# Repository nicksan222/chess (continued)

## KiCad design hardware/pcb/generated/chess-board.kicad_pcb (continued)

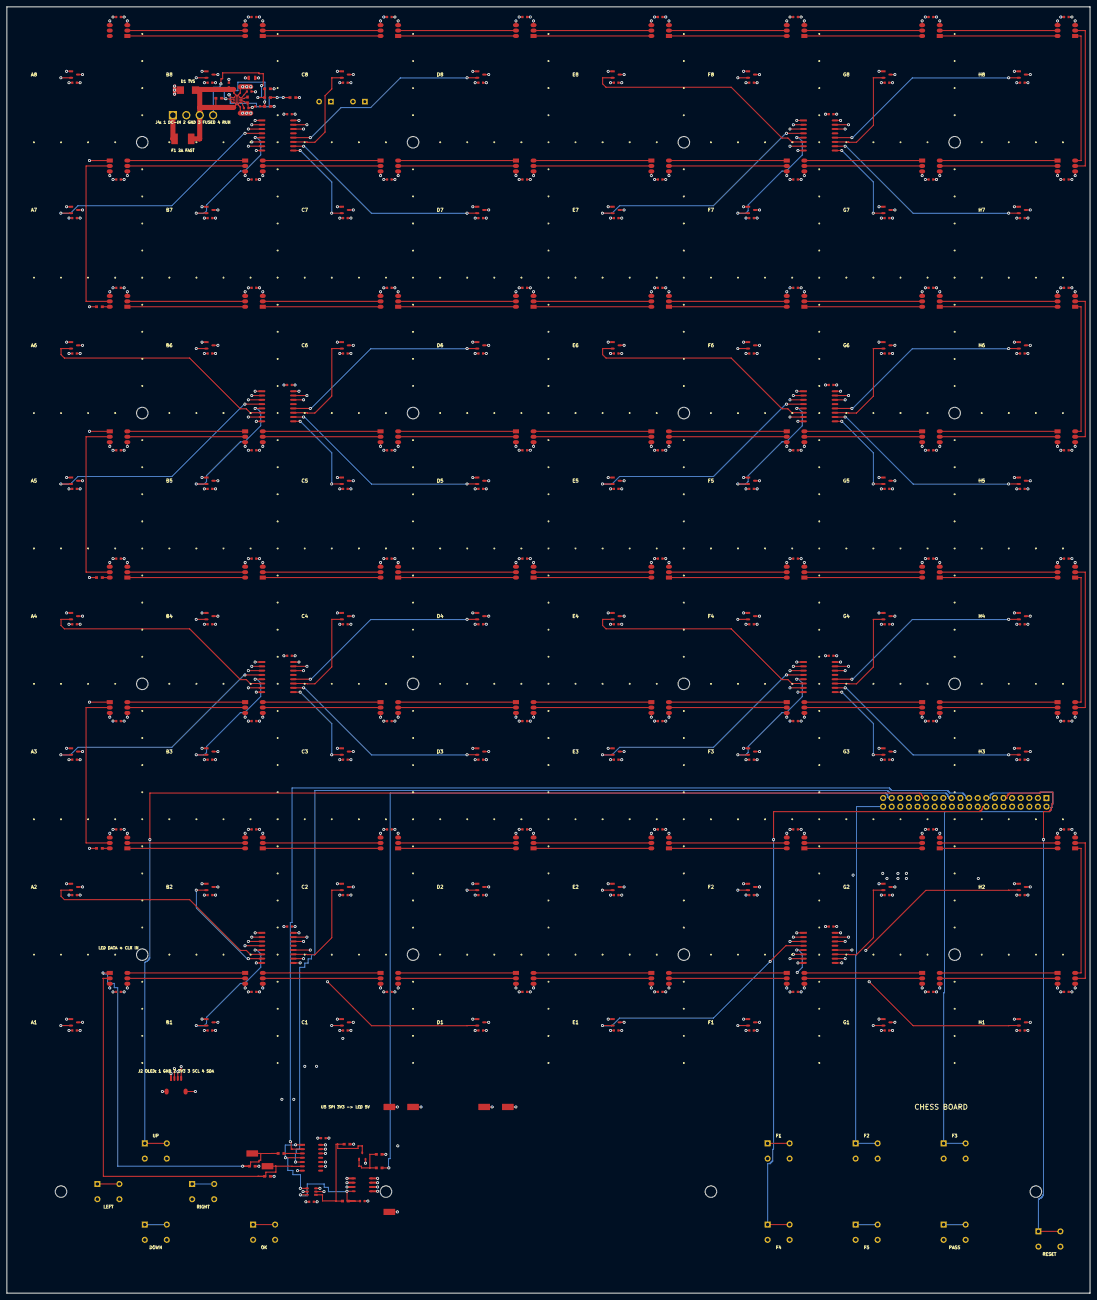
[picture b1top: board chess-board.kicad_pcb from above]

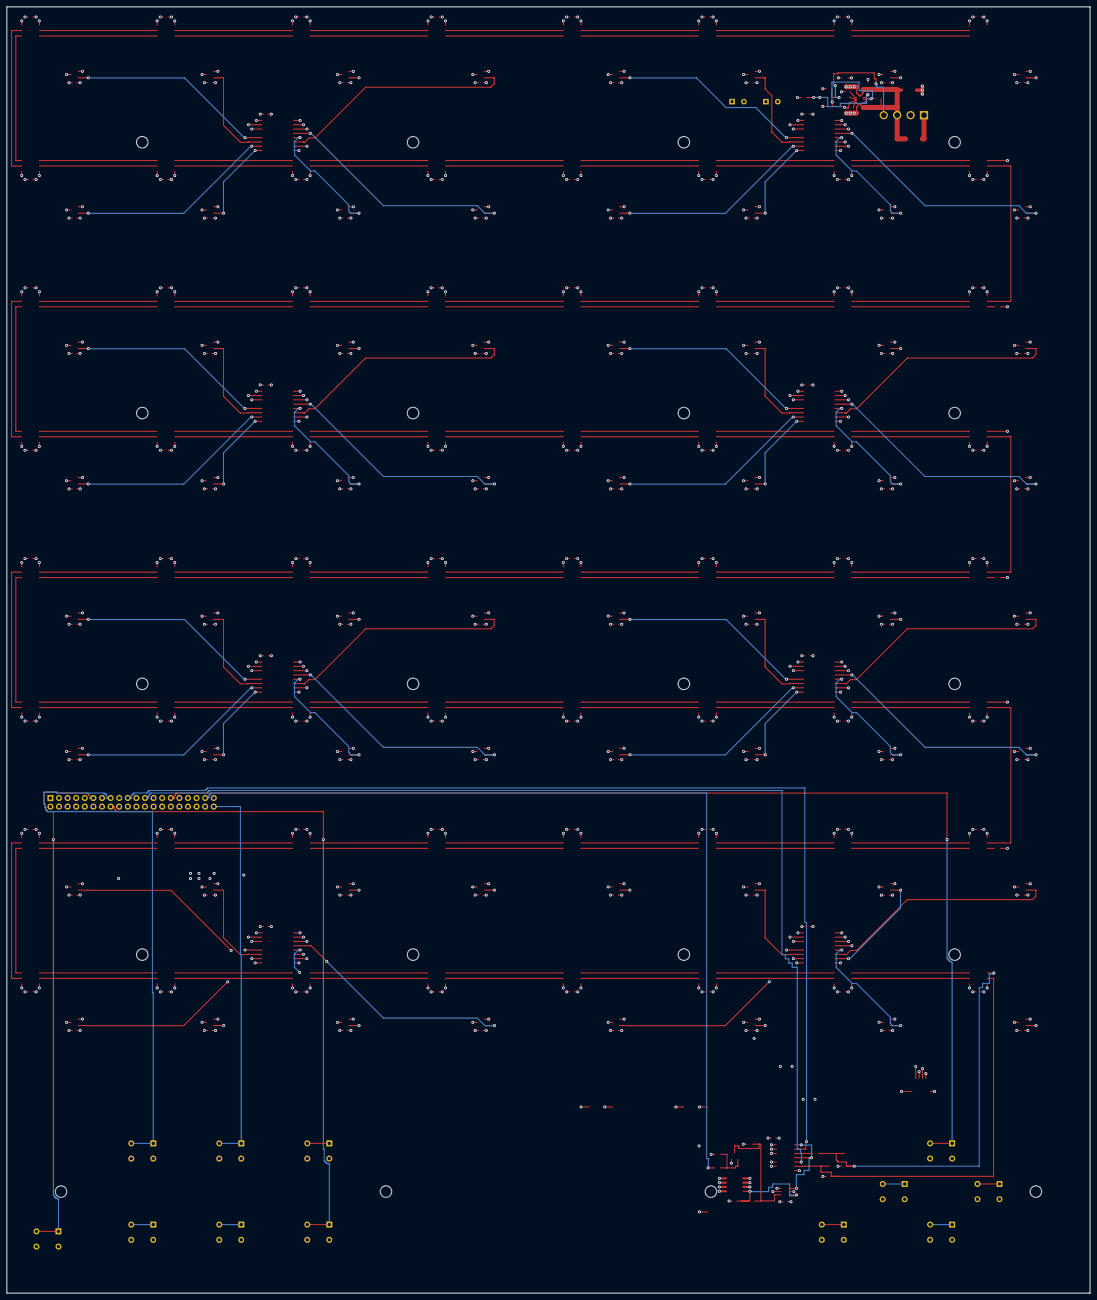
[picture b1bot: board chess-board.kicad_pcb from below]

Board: 8 copper layers, 320.0 x 380.0 mm, 347 parts (4 on the bottom side), 229 nets.

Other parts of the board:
H1, H2, H3, H4, H5, H6, H7, H8, H9, H10, H11, H12, H13, H14, H15, H16, H17, H18, H19, H20: Mounting hole

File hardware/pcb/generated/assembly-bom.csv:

Quantity,Designators,Manufacturer,Manufacturer Part Number,Package,Type
12,"SW1, SW10, SW11, SW12, SW2, SW3, SW4, SW5, SW6, SW7, SW8, SW9",E-Switch,TL1105CF100Q,6x6 mm THT,Through-hole
7,"TP1, TP2, TP3, TP4, TP5, TP6, TP7",Harwin,S1751-46R,SMD test point,SMD
1,J4,JST,B4PS-VH,VH 4P side entry THT,Through-hole
1,J2,JST,SM04B-SRSS-TB,SH 4P side entry SMD,SMD
1,F1,Littelfuse,0453002.MR,2410 fuse,SMD
1,D1,Littelfuse,SMBJ12CA,SMB (DO-214AA),SMD
64,"U10, U11, U12, U13, U14, U15, U16, U17, U18, U19, U20, U21, U22, U23, U24, U25, U26, U27, U28, U29, U30, U31, U32, U33, U34, U35, U36, U37, U38, U39, U40, U41, U42, U43, U44, U45, U46, U47, U48, U49, U50, U51, U52, U53, U54, U55, U56, U57, U58, U59, U6, U60, U61, U62, U63, U64, U65, U66, U67, U68, U69, U7, U8, U9",Opsco Optoelectronics,SK9822-A,PLCC-6 5050,SMD
2,"C1, C140",Rubycon,10ZLJ560M8X11.5,radial 8 mm,Through-hole
1,J1,Sullins Connector Solutions,PPPC202LFBN-RC,2x20 2.54 mm THT,Through-hole
64,"HS1, HS10, HS11, HS12, HS13, HS14, HS15, HS16, HS17, HS18, HS19, HS2, HS20, HS21, HS22, HS23, HS24, HS25, HS26, HS27, HS28, HS29, HS3, HS30, HS31, HS32, HS33, HS34, HS35, HS36, HS37, HS38, HS39, HS4, HS40, HS41, HS42, HS43, HS44, HS45, HS46, HS47, HS48, HS49, HS5, HS50, HS51, HS52, HS53, HS54, HS55, HS56, HS57, HS58, HS59, HS6, HS60, HS61, HS62, HS63, HS64, HS7, HS8, HS9",Texas Instruments,DRV5032FCDBZR,SOT-23-3,SMD
1,U5,Texas Instruments,SN74AHCT125DR,SOIC-14 1.27 mm,SMD
1,U75,Texas Instruments,SN74LVC1G97DBVR,SOT-23-6 (DBV),SMD
8,"U1, U2, U3, U4, U70, U71, U72, U73",Texas Instruments,TCA9554DWR,SOIC-16W 1.27 mm,SMD
1,U74,Texas Instruments,TPS259474ARPWR,VQFN-HR-10 RPW 2x2 mm,SMD
1,Q1,Vishay Siliconix,Si4403DDY-T1-GE3,SO-8 1.27 mm,SMD
1,C141,Yageo,CC0603KRX7R8BB105,0603 (1608 metric),SMD
1,C143,Yageo,CC0603KRX7R9BB102,0603 (1608 metric),SMD
3,"C142, C144, C145",Yageo,CC0603KRX7R9BB103,0603 (1608 metric),SMD
138,"C10, C100, C101, C102, C103, C104, C105, C106, C107, C108, C109, C11, C110, C111, C112, C113, C114, C115, C116, C117, C118, C119, C12, C120, C121, C122, C123, C124, C125, C126, C127, C128, C129, C13, C130, C131, C132, C133, C134, C135, C136, C137, C138, C139, C14, C146, C15, C16, C17, C18, C19, C20, C21, C22, C23, C24, C25, C26, C27, C28, C29, C3, C30, C31, C32, C33, C34, C35, C36, C37, C38, C39, C4, C40, C41, C42, C43, C44, C45, C46, C47, C48, C49, C5, C50, C51, C52, C53, C54, C55, C56, C57, C58, C59, C6, C60, C61, C62, C63, C64, C65, C66, C67, C68, C69, C7, C70, C71, C72, C73, C74, C75, C76, C77, C78, C79, C8, C80, C81, C82, C83, C84, C85, C86, C87, C88, C89, C9, C90, C91, C92, C93, C94, C95, C96, C97, C98, C99",Yageo,CC0603KRX7R9BB104,0603 (1608 metric),SMD
1,C2,Yageo,CC0805KKX5R6BB106,0805 (2012 metric),SMD
2,"R14, R16",Yageo,RC0603FR-07100KL,0603 (1608 metric),SMD
3,"R15, R17, R18",Yageo,RC0603FR-0710KL,0603 (1608 metric),SMD
1,R3,Yageo,RC0603FR-071K65L,0603 (1608 metric),SMD
2,"R13, R8",Yageo,RC0603FR-071KL,0603 (1608 metric),SMD
1,R7,Yageo,RC0603FR-07261KL,0603 (1608 metric),SMD
4,"R10, R11, R12, R9",Yageo,RC0603FR-0756RL,0603 (1608 metric),SMD
1,R5,Yageo,RT0603BRD07169KL,0603 (1608 metric),SMD
2,"R4, R6",Yageo,RT0603BRD07604KL,0603 (1608 metric),SMD
1,Q2,onsemi,BSS138LT1G,SOT-23 (TO-236),SMD

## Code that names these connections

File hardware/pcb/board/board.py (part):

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HOST_HEADER_CONNECTIONS: dict[RaspberryPiHeaderPin, BoardNet] = {
    RaspberryPiHeaderPin.THREE_VOLTS_THREE: BoardNet.THREE_VOLTS_THREE,
    RaspberryPiHeaderPin.FIVE_VOLTS: BoardNet.FIVE_VOLTS,
    RaspberryPiHeaderPin.I2C_SDA: BoardNet.I2C_SDA,
    RaspberryPiHeaderPin.FIVE_VOLTS_ALT: BoardNet.FIVE_VOLTS,
    RaspberryPiHeaderPin.I2C_SCL: BoardNet.I2C_SCL,
    RaspberryPiHeaderPin.GROUND_6: BoardNet.GROUND,
    RaspberryPiHeaderPin.GROUND_9: BoardNet.GROUND,
    RaspberryPiHeaderPin.BUTTON_RESET_GPIO17: BoardNet.BTN_RESET,
    RaspberryPiHeaderPin.GROUND_14: BoardNet.GROUND,
    RaspberryPiHeaderPin.BUTTON_F3_GPIO22: BoardNet.BTN_F3,
    RaspberryPiHeaderPin.BUTTON_F4_GPIO23: BoardNet.BTN_F4,
    RaspberryPiHeaderPin.THREE_VOLTS_THREE_ALT: BoardNet.THREE_VOLTS_THREE,
    RaspberryPiHeaderPin.BUTTON_F5_GPIO24: BoardNet.BTN_F5,
    RaspberryPiHeaderPin.SPI_DATA_GPIO10: BoardNet.SPI_DATA_3V3,
    RaspberryPiHeaderPin.GROUND_20: BoardNet.GROUND,
    RaspberryPiHeaderPin.SPI_CLOCK_GPIO11: BoardNet.SPI_CLK_3V3,
    RaspberryPiHeaderPin.GROUND_25: BoardNet.GROUND,
    RaspberryPiHeaderPin.BUTTON_UP_GPIO5: BoardNet.BTN_UP,
    RaspberryPiHeaderPin.GROUND_30: BoardNet.GROUND,
    RaspberryPiHeaderPin.BUTTON_DOWN_GPIO6: BoardNet.BTN_DOWN,
    RaspberryPiHeaderPin.BUTTON_LEFT_GPIO12: BoardNet.BTN_LEFT,
    RaspberryPiHeaderPin.BUTTON_RIGHT_GPIO13: BoardNet.BTN_RIGHT,
    RaspberryPiHeaderPin.GROUND_34: BoardNet.GROUND,
    RaspberryPiHeaderPin.BUTTON_PASS_GPIO19: BoardNet.BTN_PASS,
    RaspberryPiHeaderPin.BUTTON_OK_GPIO16: BoardNet.BTN_OK,
    RaspberryPiHeaderPin.LED_EN_GPIO26: BoardNet.LED_EN,
    RaspberryPiHeaderPin.BUTTON_F1_GPIO20: BoardNet.BTN_F1,
    RaspberryPiHeaderPin.GROUND_39: BoardNet.GROUND,
    RaspberryPiHeaderPin.BUTTON_F2_GPIO21: BoardNet.BTN_F2,
}


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) -> BoardLayout[BoardNet]:
    labels = [
        Label("CHESS BOARD", _layout_point(116, -165), 1.5),
        Label("J4: 1 DC-IN 2 GND 3 FUSED 4 RUN", _layout_point(-105, 125.9), 0.8),
        Label("U5 SPI 3V3 -> LED 5V", _layout_point(-60, -165), 0.8),
        Label("LED DATA + CLK IN", _layout_point(-127, -118), 0.8),
    ]
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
